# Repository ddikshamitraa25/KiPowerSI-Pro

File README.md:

# KiPowerSI Pro: KiCad 9 Plugin
## Intelligent Power Distribution Network (PDN), DC IR-Drop & Trace Thermal Parasitics Analyzer

[-brightgreen.svg)](#-automated-unit-testing)

---

##  Internship Submission Details
- **Program**: IIT Bombay FOSSEE eSim Semester Long Internship (Autumn 2026)
- **Task Category**: Task 6 - KiCad Plugin Development (CSE & Electronics Integration)
- **Target EDA Platform**: KiCad 9.0+ (`pcbnew` Python ActionPlugin System)
- **Submission Email**: `contact-esim@fossee.in`
- **Email Subject**: `eSim Semester Long Internship - Autumn 2026 Submission Task 6`

---

## 👨‍💻 Executive Summary & Problem Motivation

Modern Printed Circuit Board (PCB) designs feature high-density integrated circuits (FPGA, MCU, SoC) operating at low core voltages ($1.0\text{V} - 3.3\text{V}$) and drawing high transient currents. At these operational levels, even minor copper trace resistances introduce significant voltage drops (**DC IR-Drop**) and localized trace heating (**Joule Heating** $I^2R$), leading to signal instability, unexpected resets, and thermal degradation.

Commercial co-simulation tools (such as Ansys SIwave or Cadence Sigrity) are proprietary and prohibitively expensive for academic institutions and open-source hardware developers.

**KiPowerSI Pro** bridges **Computer Science** (Graph Algorithms, Finite Difference Nodal Linear Matrix Solvers, Geometric Parsing) and **Electronics Engineering** (IPC-2221 Trace Thermal Equations, Transmission Line Parasitics, Ohm's Nodal Analysis) into a clean, automated **KiCad 9 Action Plugin**.

---

##  Key Features & Module Overview

| Feature | Engineering & CS Description | Relevant File |
| :--- | :--- | :--- |
| **Spatial Net Connectivity Graph Extraction** | Automatically parses track segments, via barrels, copper zones, and pads into a topological directed net graph $G=(V,E)$. Merges co-located endpoints within epsilon spatial tolerance. | [`graph_extractor.py`](kipowersi/graph_extractor.py) |
| **2D Nodal Linear Resistance Matrix Solver** | Assembles the global nodal conductance matrix $\mathbf{G} \cdot \mathbf{V} = \mathbf{I}$ using Kirchhoff's Current Law (KCL). Computes exact node potentials, branch currents, and current densities ($J$ in $\text{A/mm}^2$). | [`ir_drop_solver.py`](kipowersi/ir_drop_solver.py) |
| **IPC-2221 Trace Thermal Hotspot Engine** | Calculates steady-state trace temperature rise ($\Delta T$) using standard empirical IPC-2221 formulas for internal and external copper layers. Identifies thermal bottlenecks. | [`thermal_engine.py`](kipowersi/thermal_engine.py) |
| **Transmission Line Signal Integrity (SI) Engine** | Estimates Surface Microstrip and Internal Stripline characteristic impedance ($Z_0$), propagation delay ($t_{pd}$), per-unit length $L, C$, and capacitive crosstalk factor ($K_C$). | [`signal_integrity.py`](kipowersi/signal_integrity.py) |
| **Automated PDN & SI DRC Rule Engine** | Flags nets exceeding IR-drop limits ($>3\%$), current density limits ($>30\text{ A/mm}^2$), thermal rise limits ($>15\text{°C}$), and impedance mismatches ($Z_0 \neq 50\Omega$). | [`drc_rules.py`](kipowersi/drc_rules.py) |
| **Interactive HTML Report & SVG Layout Exporter** | Generates self-contained interactive HTML dashboards with embedded CSS, color-coded vector SVG layout thermal heatmaps, and tabular CSV spreadsheet exports. | [`report_generator.py`](kipowersi/report_generator.py) |
| **Dual Execution Interface (KiCad 9 + Headless CLI)** | Integrates directly into KiCad 9 PCB Editor via wxPython modal dialog, with full standalone Tkinter GUI and CLI fallback for headless testing. | [`gui.py`](kipowersi/gui.py) / [`plugin.py`](kipowersi/plugin.py) |

---

## 🔀 System Architecture & Process Flowcharts

### High-Level System Workflow

```
+-----------------------------------------------------------------------------------+
|                              KiCad 9 PCB Editor                                   |
|                        (pcbnew Python Action Plugin API)                          |
+-----------------------------------------------------------------------------------+
                                         |
                                         v
+-----------------------------------------------------------------------------------+
|                        1. Spatial Board Net Graph Extractor                       |
|           Parses TRACK, VIA, PAD, ZONE into Topological Graph G = (V, E)           |
+-----------------------------------------------------------------------------------+
                                         |
            +----------------------------+----------------------------+
            |                            |                            |
            v                            v                            v
+------------------------+  +------------------------+  +---------------------------+
| 2. 2D Nodal IR-Drop    |  | 3. IPC-2221 Trace      |  | 4. Transmission Line      |
|    Matrix Solver       |  |    Thermal Engine      |  |    Signal Integrity (SI)  |
|    (G * V = I)         |  |    (Joule Heat ΔT)     |  |    (Z0, L, C, Kc)          |
+------------------------+  +------------------------+  +---------------------------+
            |                            |                            |
            +----------------------------+----------------------------+
                                         |
                                         v
+-----------------------------------------------------------------------------------+
|                      5. Automated PDN & SI DRC Rule Engine                        |
|        (Evaluates IR-drop %, Current Density A/mm², ΔT °C, Z0 impedance)          |
+-----------------------------------------------------------------------------------+
                                         |
                                         v
+-----------------------------------------------------------------------------------+
|                   6. Interactive Presentation & Exporter Pipeline                 |
|   - Native wxPython KiCad Modal Window / Standalone Tkinter GUI                   |
|   - Scalable Vector SVG Layout Heatmap (Green=Safe, Amber=Warning, Red=Critical)  |
|   - Self-Contained Interactive HTML Dashboard & CSV Spreadsheet Export            |
+-----------------------------------------------------------------------------------+
```

---

##  Mathematical & Electronics Foundations

### 1. Temperature-Corrected Copper Resistance
The electrical resistance $R$ of a trace segment of length $L$, width $w$, and copper thickness $t$ is calculated as:
$$R = \rho(T) \cdot \frac{L}{w \cdot t}$$

Where temperature-adjusted resistivity $\rho(T)$ is given by:
$$\rho(T) = \rho_{20} \cdot [1 + \alpha (T_{ambient} - 20^\circ\text{C})]$$

- $\rho_{20} = 1.72 \times 10^{-8}\ \Omega\cdot\text{m}$ (Annealed copper resistivity at 20°C)
- $\alpha = 0.00393 / ^\circ\text{C}$ (Temperature coefficient of resistance)

---

### 2. Nodal Conductance System Solvers ($\mathbf{G} \cdot \mathbf{V} = \mathbf{I}$)
Applying Kirchhoff's Current Law at each node $i$:
$$\sum_{j \in N(i)} g_{ij} (V_i - V_j) = I_{ext, i}$$

Where branch conductance $g_{ij} = \frac{1}{R_{ij}}$. Assembling into linear system form:
$$\mathbf{G} \cdot \mathbf{V} = \mathbf{I}$$

Boundary conditions fix the VRM source pad voltage to $V_{source}$ (e.g., $5.0\text{V}$), and matrix inversion yields all internal node potentials $\mathbf{V}$.

---

### 3. IPC-2221 Trace Thermal Heating Formula
Trace temperature rise ($\Delta T$ in $\text{°C}$) under RMS current load is evaluated using empirical IPC-2221 equations:
$$\Delta T = \left( \frac{I_{RMS}}{k \cdot A^{0.725}} \right)^{\frac{1}{0.44}}$$

- $I_{RMS}$ is branch current in Amperes.
- $A$ is trace cross-sectional area in $\text{mil}^2$ ($1\text{ mm}^2 = 1550\text{ mil}^2$).
- $k = 0.048$ for external surface copper layers (F.Cu, B.Cu).
- $k = 0.024$ for internal copper layers (In1.Cu, In2.Cu).

---

### 4. Surface Microstrip Transmission Line Impedance ($Z_0$)
For a surface trace of width $w$ routed over a ground plane at height $h$ with dielectric constant $\varepsilon_r$:
$$Z_0 = \frac{87}{\sqrt{\varepsilon_r + 1.41}} \cdot \ln \left( \frac{5.98 \cdot h}{0.8 \cdot w + t} \right) \quad [\Omega]$$

Propagation delay ($t_{pd}$):
$$t_{pd} = 3.333 \cdot \sqrt{0.475 \cdot \varepsilon_r + 0.67} \quad [\text{ns/m}]$$

---

##  Repository Deliverables & Structure

```
KiCad Plugin Development/
├── README.md                  # Comprehensive Overview, Mathematical Theory & Guide
├── DESIGN_DOCUMENT.md         # Detailed Software Architecture & Math Derivation
├── PROPOSAL.md                # Formal Proposal for IIT Bombay FOSSEE Selection
├── INSTALL.md                 # Step-by-Step Installation Manual for Windows, Linux, macOS
├── LICENSE                    # MIT Open Source License
├── requirements.txt           # Python Project Dependencies
├── setup.py                   # Standard Setuptools Package Installer
├── .gitignore                 # Git ignore rules for bytecode & outputs
├── kipowersi/                 # Core Python Package
│   ├── __init__.py            # Package Init & ActionPlugin Auto-Loader
│   ├── plugin.py              # KiCad 9 pcbnew.ActionPlugin & CLI Entrypoint
│   ├── gui.py                 # wxPython KiCad Dialog & Standalone Tkinter GUI
│   ├── graph_extractor.py     # KiCad Board Parser & Layout Net Graph Extractor
│   ├── ir_drop_solver.py      # 2D Nodal Resistance Mesh Solver (G * V = I)
│   ├── thermal_engine.py      # IPC-2221 Trace Heating & Thermal Hotspot Engine
│   ├── signal_integrity.py    # Microstrip/Stripline Impedance Z0 & Crosstalk Engine
│   ├── drc_rules.py           # Automated PDN & SI DRC Rule Checker
│   └── report_generator.py   # HTML Report, SVG Vector Heatmap, & CSV Exporter
├── sample_board/              # Test KiCad 9 PCB Project File
│   ├── test_power_board.kicad_pcb # PCB layout with power rails (+5V, +3V3, GND)
│   └── test_power_board.kicad_pro # KiCad 9 project file
└── tests/                     # Self-Contained Automated Unit Test Suite
    ├── test_graph_extractor.py
    ├── test_ir_drop_solver.py
    ├── test_thermal_engine.py
    ├── test_signal_integrity.py
    ├── test_drc_rules.py
    └── test_report_generator.py
```

---

## 🛠️ Step-by-Step Installation & Usage Guide

### Option 1: Native KiCad 9 Plugin Mode

1. Locate your KiCad 9 scripting plugins folder:
   - **Windows**: `%APPDATA%\kicad\9.0\scripting\plugins\`
   - **Linux**: `~/.local/share/kicad/9.0/scripting/plugins/`
   - **macOS**: `~/Library/Preferences/kicad/9.0/scripting/plugins/`

2. Copy the [`kipowersi`](kipowersi/) directory into the plugins folder.

3. Launch **KiCad 9 PCB Editor** -> Go to **Tools -> External Plugins -> Refresh Plugins**. Click **KiPowerSI Pro** to open the modal UI window.

---

### Option 2: Standalone CLI / GUI Mode

You can run **KiPowerSI Pro** outside of KiCad using standard Python:

```bash
# 1. Run CLI analysis on the provided sample board
python -m kipowersi.plugin --board sample_board/test_power_board.kicad_pcb --net +5V --voltage 5.0 --current 2.0

# 2. Launch Standalone Tkinter GUI
python -m kipowersi.gui
```

---

## 🧪 Automated Unit Testing

The project features a self-contained unit test suite in [`tests/`](tests/) requiring zero external testing packages.

Run the test suite:
```bash
python -m unittest discover -s tests -v
```

Expected Terminal Output:
```text
test_drc_rules_evaluation (test_drc_rules.TestDRCRules.test_drc_rules_evaluation) ... ok
test_extract_from_sample_file (test_graph_extractor.TestGraphExtractor.test_extract_from_sample_file) ... ok
test_synthetic_graph_building (test_graph_extractor.TestGraphExtractor.test_synthetic_graph_building) ... ok
test_ir_drop_solver_accuracy (test_ir_drop_solver.TestIRDropSolver.test_ir_drop_solver_accuracy) ... ok
test_report_generator (test_report_generator.TestReportGenerator.test_report_generator) ... ok
test_signal_integrity_microstrip (test_signal_integrity.TestSignalIntegrity.test_signal_integrity_microstrip) ... ok
test_thermal_engine_calculations (test_thermal_engine.TestThermalEngine.test_thermal_engine_calculations) ... ok

----------------------------------------------------------------------
Ran 7 tests in 0.270s

OK
```

---

## 📜 License & Contact

Distributed under the **MIT License**. See [`LICENSE`](LICENSE) for details.

Designed and developed for the **FOSSEE eSim Team at IIT Bombay**.  
**Submission Email**: `contact-esim@fossee.in`  
**Subject**: `eSim Semester Long Internship - Autumn 2026 Submission Task 6`

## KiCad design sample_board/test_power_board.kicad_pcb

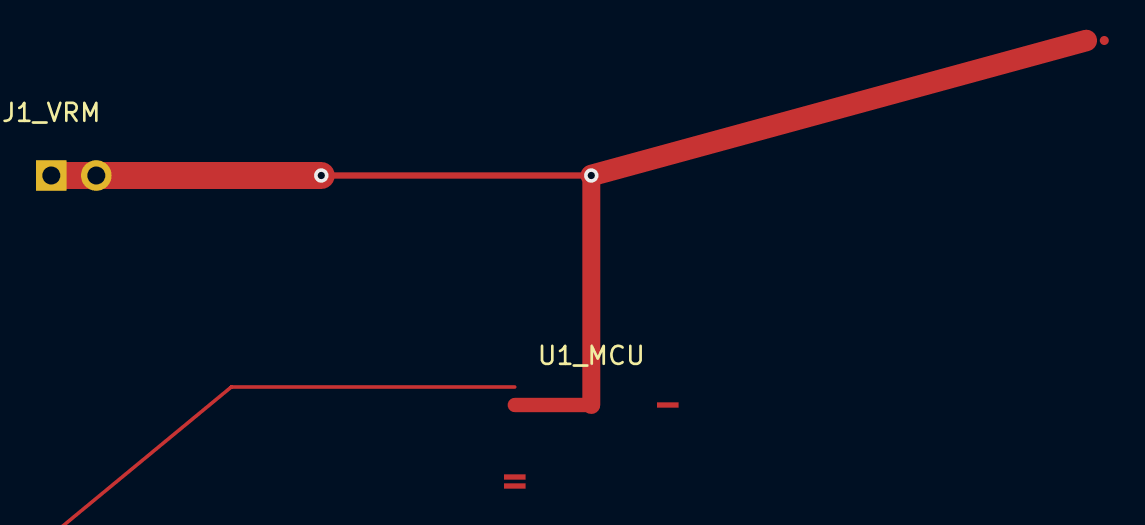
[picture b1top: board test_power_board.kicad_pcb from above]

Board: 4 copper layers, 3 parts (0 on the bottom side), 2 nets.

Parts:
J1_VRM: JST_XH_B2B-XH-A_1x02_P2.50mm_Vertical
U1_MCU: TQFP-48_7x7mm_P0.5mm
U2_FPGA: BGA-256_17x17_1.0mm

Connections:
+5V: J1_VRM.1, U1_MCU.1, U2_FPGA.A1
GND: J1_VRM.2, U1_MCU.24, U2_FPGA.B1
